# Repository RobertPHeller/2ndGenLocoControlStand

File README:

This is a model diesel locomotive control stand (more or less typical of a 2nd 
generation diesel locomotive).

Files / Directories:

2ndGenLocoControlStand.dxf, 2ndGenLocoControlStand.gcad, and 
2ndGenLocoControlStand.tcl relate to the 3D model of the front panel (based on 
a Hammond Manucafturing RL6685 enclosure).

The ESP32ControlStand directory contains the ESP32 (TTGO-T1) based design, the 
electronics are in KiCad form (Version: 2013.06.11).  The 
ESP32ControlStand/ESP32ControlStand_Node directory contains the OpenMRN code 
(C++, Arduino style using the OpenMRNLite library).

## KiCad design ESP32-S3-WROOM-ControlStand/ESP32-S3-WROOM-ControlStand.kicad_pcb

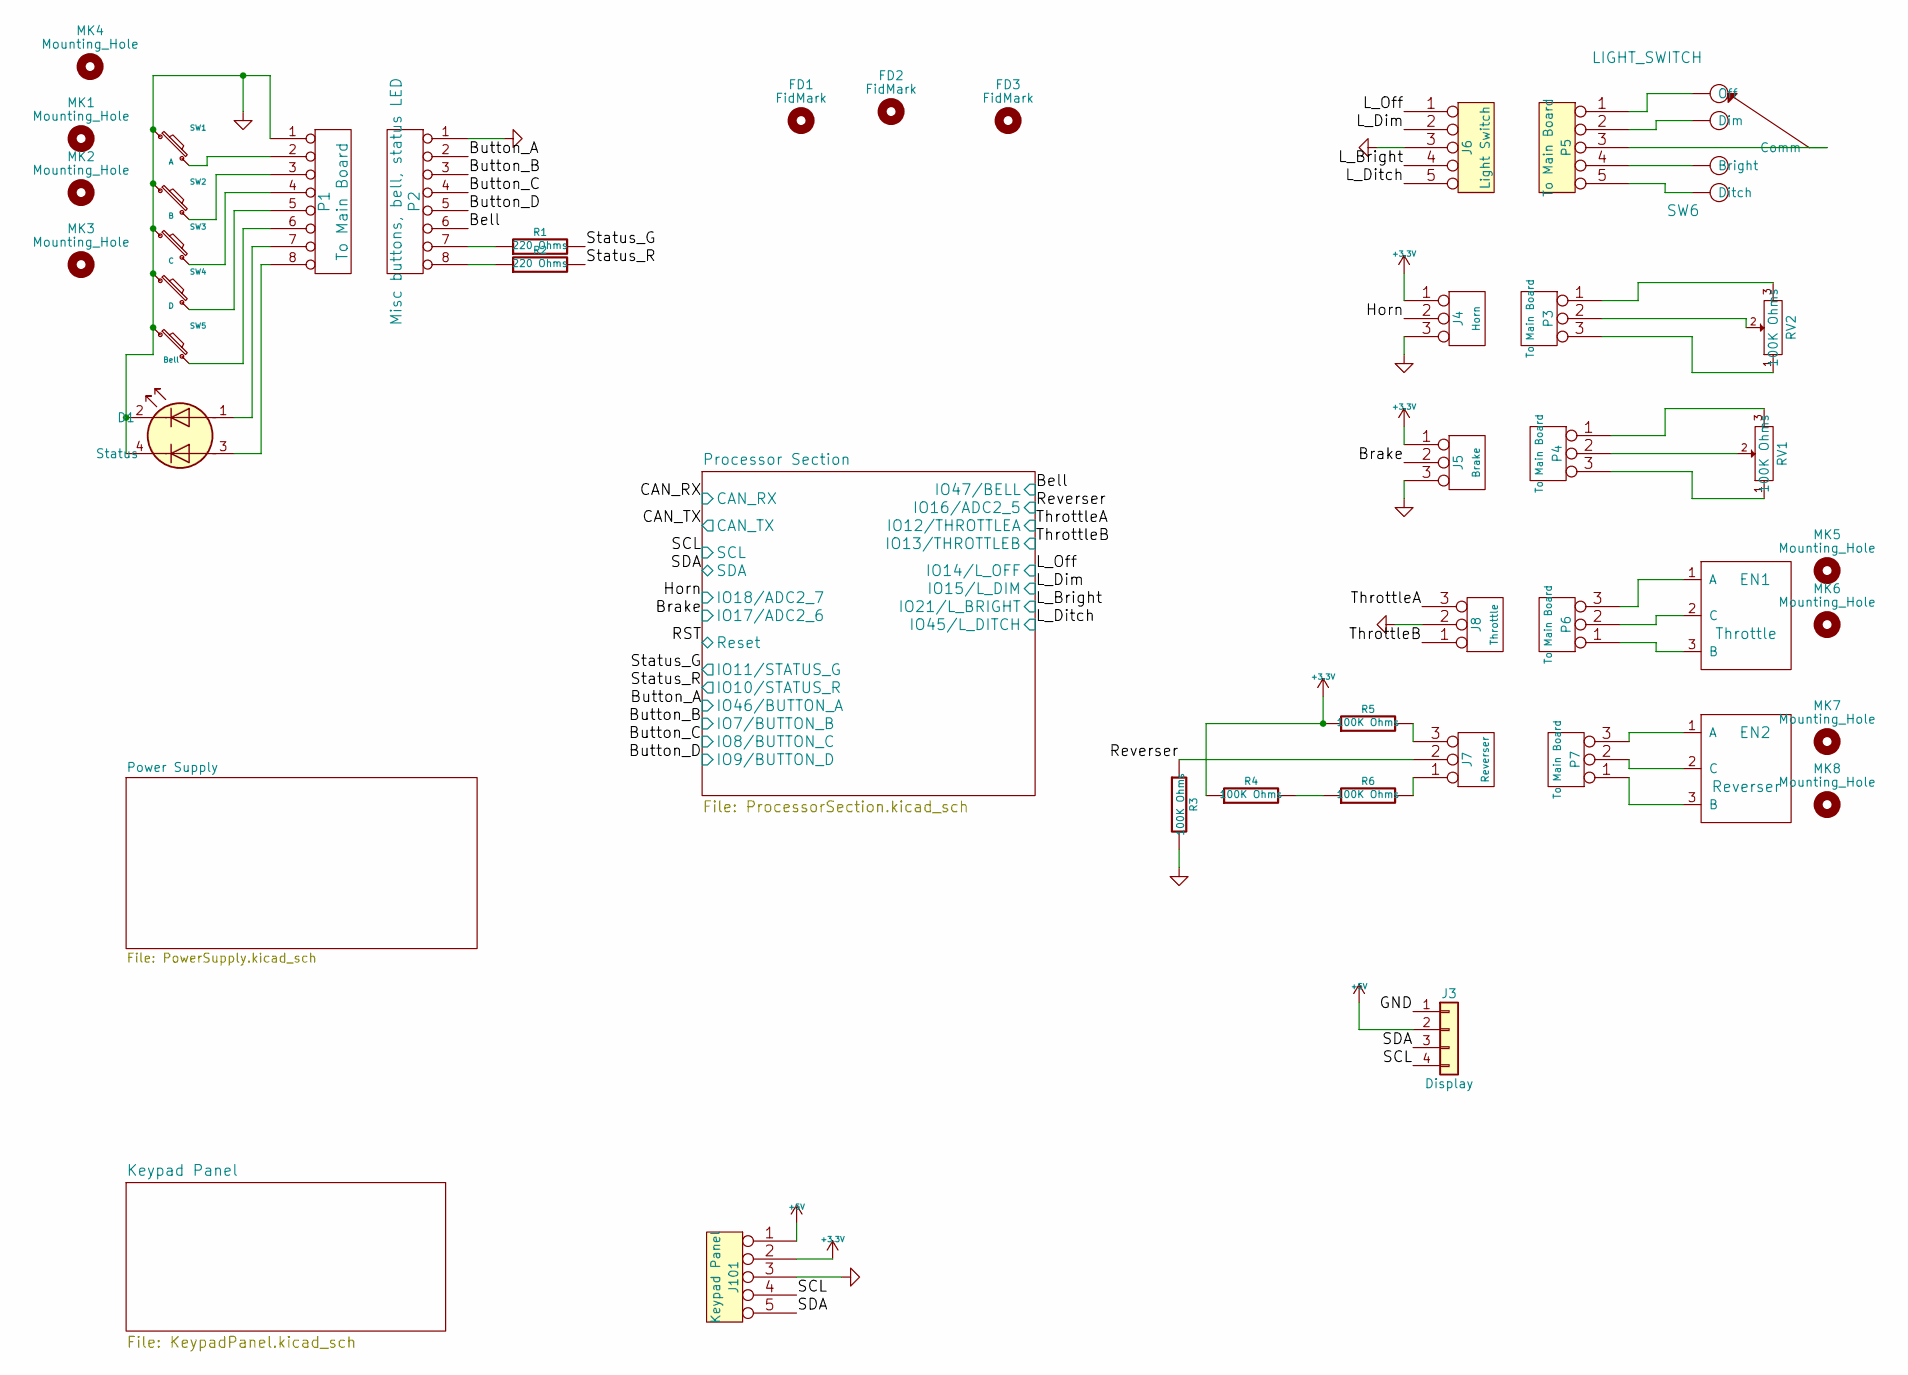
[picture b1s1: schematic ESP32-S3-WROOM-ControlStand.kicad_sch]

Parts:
D1: Status; APHB1608CGKSURKC; Mouser Part Number 604-APHB1608CGKSURKC
EN1: Throttle; Series25L-Encoder; Mouser Part Number 706-25LB10-Q
EN2: Reverser; ALPSEC12C; Mouser Part Number 652-PEC11R4325FN0012
FD1, FD2, FD3: FidMark; Fiducial_1mm_Dia_2.54mm_Outer_CopperTop
J3: Display; JST_PH_B4B-PH-K_1x04_P2.00mm_Vertical; Manufacturer_Part_Number B4B-PH-SM4-TB
J4: Horn; Pin_Header_Straight_1x03_Pitch2.54mm; Mouser Part Number 649-1012937890301BLF
J5: Brake; Pin_Header_Straight_1x03_Pitch2.54mm; Mouser Part Number 649-1012937890301BLF
J6: Light Switch; Pin_Header_Straight_1x05_Pitch2.54mm; Mouser Part Number 523-G800W303018EU
J7: Reverser; Pin_Header_Straight_1x03_Pitch2.54mm; Mouser Part Number 649-1012937890301BLF
J8: Throttle; Pin_Header_Straight_1x03_Pitch2.54mm; Mouser Part Number 649-1012937890301BLF
J101: Keypad Panel; Pin_Header_Straight_1x05_Pitch2.54mm; Mouser Part Number 523-G800W303018EU
MK1, MK2, MK3, MK4, MK5, MK6, MK7, MK8: Mounting_Hole; MountingHole_2.5mm
P1: To Main Board; Pin_Header_Angled_1x08_Pitch2.54mm; Mouser Part Number 649-1012937990801BLF
P2: Misc buttons, bell, status LED; Pin_Header_Straight_1x08_Pitch2.54mm; Mouser Part Number 649-1012937890801BLF
P3, P4, P5: To Main Board
P6, P7: To Main Board; Pin_Header_Angled_1x03_Pitch2.54mm; Mouser Part Number 855-M20-9750346
R1, R2: 220 Ohms; R_0603_1608Metric; Mouser Part Number 603-AC0603FR-07220RL
R3, R4, R5, R6: 100K Ohms; R_0402_1005Metric; Mouser Part Number 279-CRGCQ0402J100K
RV1, RV2: 100K Ohms; Mouser Part Number 774-450T328F104A1A1
SW1: A; SW_SPST_EVQQ2; Mouser Part Number 667-EVQ-Q2U02W
SW2: B; SW_SPST_EVQQ2; Mouser part Number 667-EVQ-Q2U02W
SW3: C; SW_SPST_EVQQ2; Mouser Part Number 667-EVQ-Q2U02W
SW4: D; SW_SPST_EVQQ2; Mouser Part Number 667-EVQ-Q2U02W
SW5: Bell; SW_SPST_EVQQ2; Mouser Part Number 667-EVQ-Q2U02W
SW6: LIGHT_SWITCH

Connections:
+5V: J3.2, J101.1; also elsewhere on the board
/Bell: P2.6; also elsewhere on the board
/Brake: J5.2 (PM); also elsewhere on the board
/Button_A: P2.2; also elsewhere on the board
/Button_B: P2.3; also elsewhere on the board
/Button_C: P2.4; also elsewhere on the board
/Button_D: P2.5; also elsewhere on the board
/Horn: J4.2 (PM); also elsewhere on the board
/L_Bright: J6.4; also elsewhere on the board
/L_Dim: J6.2; also elsewhere on the board
/L_Ditch: J6.5; also elsewhere on the board
/L_Off: J6.1; also elsewhere on the board
/Reverser: J7.2 (PM), R3.1; also elsewhere on the board
/SCL: J3.4, J101.4; also elsewhere on the board
/SDA: J3.3, J101.5; also elsewhere on the board
/Status_G: R1.2; also elsewhere on the board
/Status_R: R2.2; also elsewhere on the board
/ThrottleA: J8.3; also elsewhere on the board
/ThrottleB: J8.1; also elsewhere on the board
GND: D1.2 (K1), D1.4 (K2), J3.1, J4.3, J5.3, J6.3, J8.2 (PM), J101.3, P1.1, P2.1, R3.2, SW1.1, SW2.1, SW3.1, SW4.1, SW5.1; also elsewhere on the board
unnamed: D1.1 (A1), P1.7
unnamed: D1.3 (A2), P1.8
unnamed: EN1.1 (A), P6.3
unnamed: EN1.2 (C), P6.2 (PM)
unnamed: EN1.3 (B), P6.1
unnamed: EN2.1 (A), P7.3
unnamed: EN2.2 (C), P7.2 (PM)
unnamed: EN2.3 (B), P7.1
unnamed: J7.1, R6.2
unnamed: J7.3, R5.2
unnamed: P1.2, SW1.2
unnamed: P1.3, SW2.2
unnamed: P1.4, SW3.2
unnamed: P1.5, SW4.2
unnamed: P1.6, SW5.2
unnamed: P2.7, R1.1
unnamed: P2.8, R2.1
unnamed: P3.1, RV2.3
unnamed: P3.2 (PM), RV2.2
unnamed: P3.3, RV2.1
unnamed: P4.1, RV1.3
unnamed: P4.2 (PM), RV1.2
unnamed: P4.3, RV1.1
unnamed: P5.1, SW6.~
unnamed: P5.2, SW6.~
unnamed: P5.3, SW6.~
unnamed: P5.4, SW6.~
unnamed: P5.5, SW6.~
unnamed: R4.2, R6.1

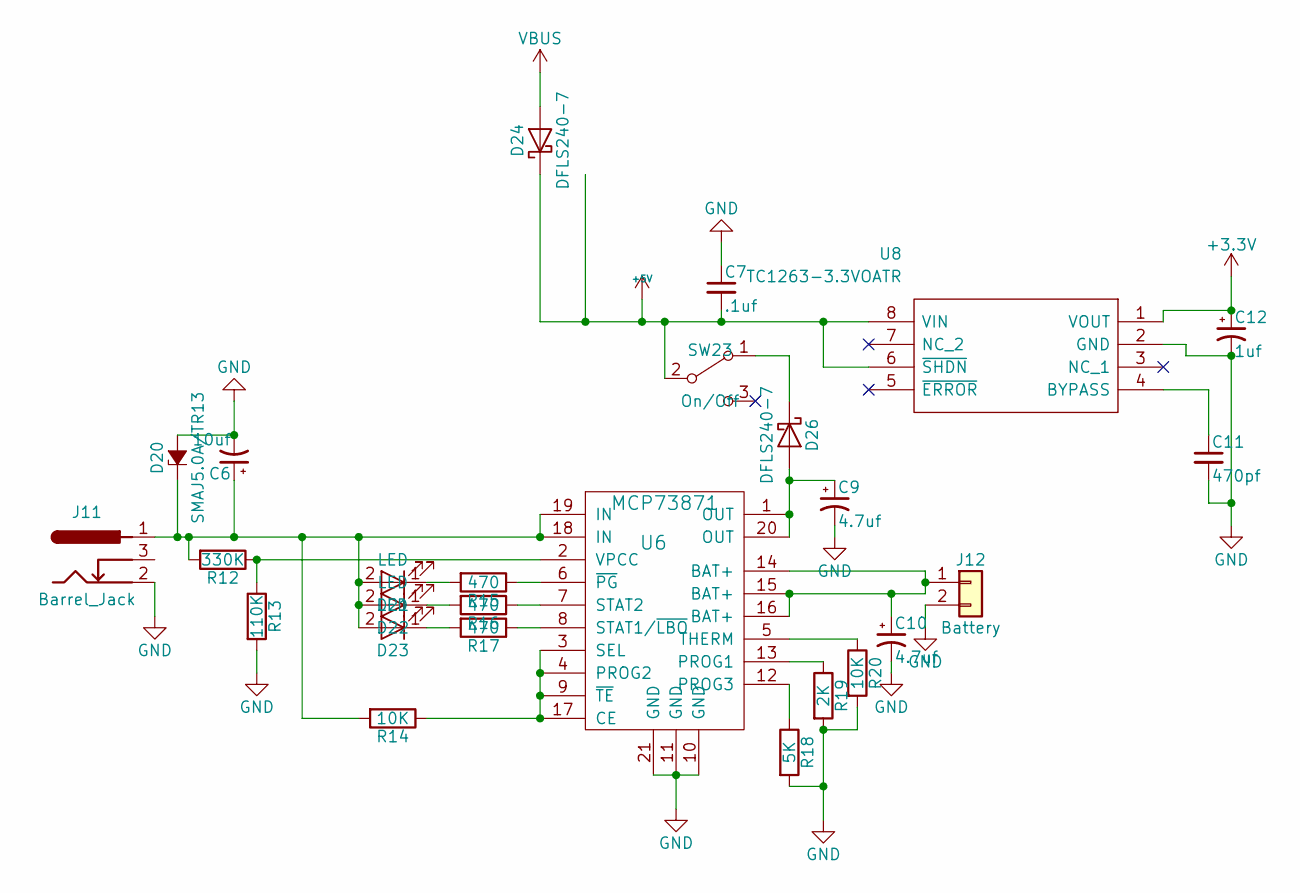
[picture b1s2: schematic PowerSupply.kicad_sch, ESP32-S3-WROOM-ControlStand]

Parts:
C6: 10uf; CP_Elec_4x5.7; Mouser Part Number 710-865080340001
C7: .1uf; C_0402; Mouser Part Number 81-GRM155R62A104KE4J
C9, C10: 4.7uf; CP_Elec_4x5.7; Mouser Part Number 710-865080640004
C11: 470pf; C_0402; Mouser Part Number 80-C0402C471K4RAUTO
C12: 1uf; C_0603_POL; Mouser Part Number 74-TMCJ1C105MTRF
D20: SMAJ5.0A/TR13; D_SMA; Mouser Part Number 603-SMAJ5.0A/TR13
D21: LED; LED_0402; Mouser Part Number 710-150040GS73220
D22: LED; LED_0402; Mouser Part Number 710-150040YS73220
D23: LED; LED_0402; Mouser Part Number 710-150040RS73220
D24, D26: DFLS240-7; D_PowerDI-123; Mouser Part Number 621-DFLS240-7
J11: Barrel_Jack; BARREL_JACK; Mouser Part Number 992-CON-SOCJ-2155
J12: Battery; JST_PH_B2B-PH-K_1x02_P2.00mm_Vertical; Manufacturer_Part_Number B2B-PH-SM4-TB
R12: 330K; R_0402; Mouser Part Number 603-AF0402FR-07330KL
R13: 110K; R_0402; Mouser Part Number 603-RC0402JR-13110KL
R14, R20: 10K; R_0402; Mouser Part Number 603-RC0402JR-0710KL
R15, R16, R17: 470; R_0402; Mouser Part Number 603-RC0402JR-07470RL
R18: 5K; R_0402; Mouser Part Number 603-RC0402FR-075KL
R19: 2K; R_0402; Mouser Part Number 603-RC0402FR-132KL
SW23: On/Off; SW_SPDT_CK-JS102011SAQN; Mouser Part Number 611-JS102011SAQN
U6: MCP73871; QFN-20-1EP_4x4mm_P0.5mm_EP2.5x2.5mm_ThermalVias; Mouser Part Number 579-MCP73871-3CAI/ML
U8: TC1263-3.3VOATR; SOIC-8W_5.3x5.3mm_P1.27mm; Manufacturer_Part_Number TC1263-3.3VOATR

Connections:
+5V: C7.2, D24.1 (K), SW23.2 (B), U8.6 (~SHDN), U8.8 (VIN); also elsewhere on the board
GND: C6.2, C7.1, C9.2, C10.2, C11.2, C12.2, D20.2 (A), J11.2, J12.2, R13.2, R18.2, R19.2, R20.2, U6.10 (GND), U6.11 (GND), U6.21 (GND), U8.2 (GND); also elsewhere on the board
unnamed: C6.1, D20.1 (K), D21.2 (A), D22.2 (A), D23.2 (A), J11.1, R12.2, R14.2, U6.18 (IN), U6.19 (IN)
unnamed: C9.1, D26.2 (A), U6.1 (OUT), U6.20 (OUT)
unnamed: C10.1, J12.1, U6.14 (BAT+), U6.15 (BAT+), U6.16 (BAT+)
unnamed: C11.1, U8.4 (BYPASS)
unnamed: D21.1 (K), R15.2
unnamed: D22.1 (K), R16.2
unnamed: D23.1 (K), R17.2
unnamed: D26.1 (K), SW23.1 (A)
unnamed: R12.1, R13.1, U6.2 (VPCC)
unnamed: R14.1, U6.3 (SEL), U6.4 (PROG2), U6.9 (~TE), U6.17 (CE)
unnamed: R15.1, U6.6 (~PG)
unnamed: R16.1, U6.7 (STAT2)
unnamed: R17.1, U6.8 (STAT1/~LBO)
unnamed: R18.1, U6.12 (PROG3)
unnamed: R19.1, U6.13 (PROG1)
unnamed: R20.1, U6.5 (THERM)
VBUS: D24.2 (A); also elsewhere on the board

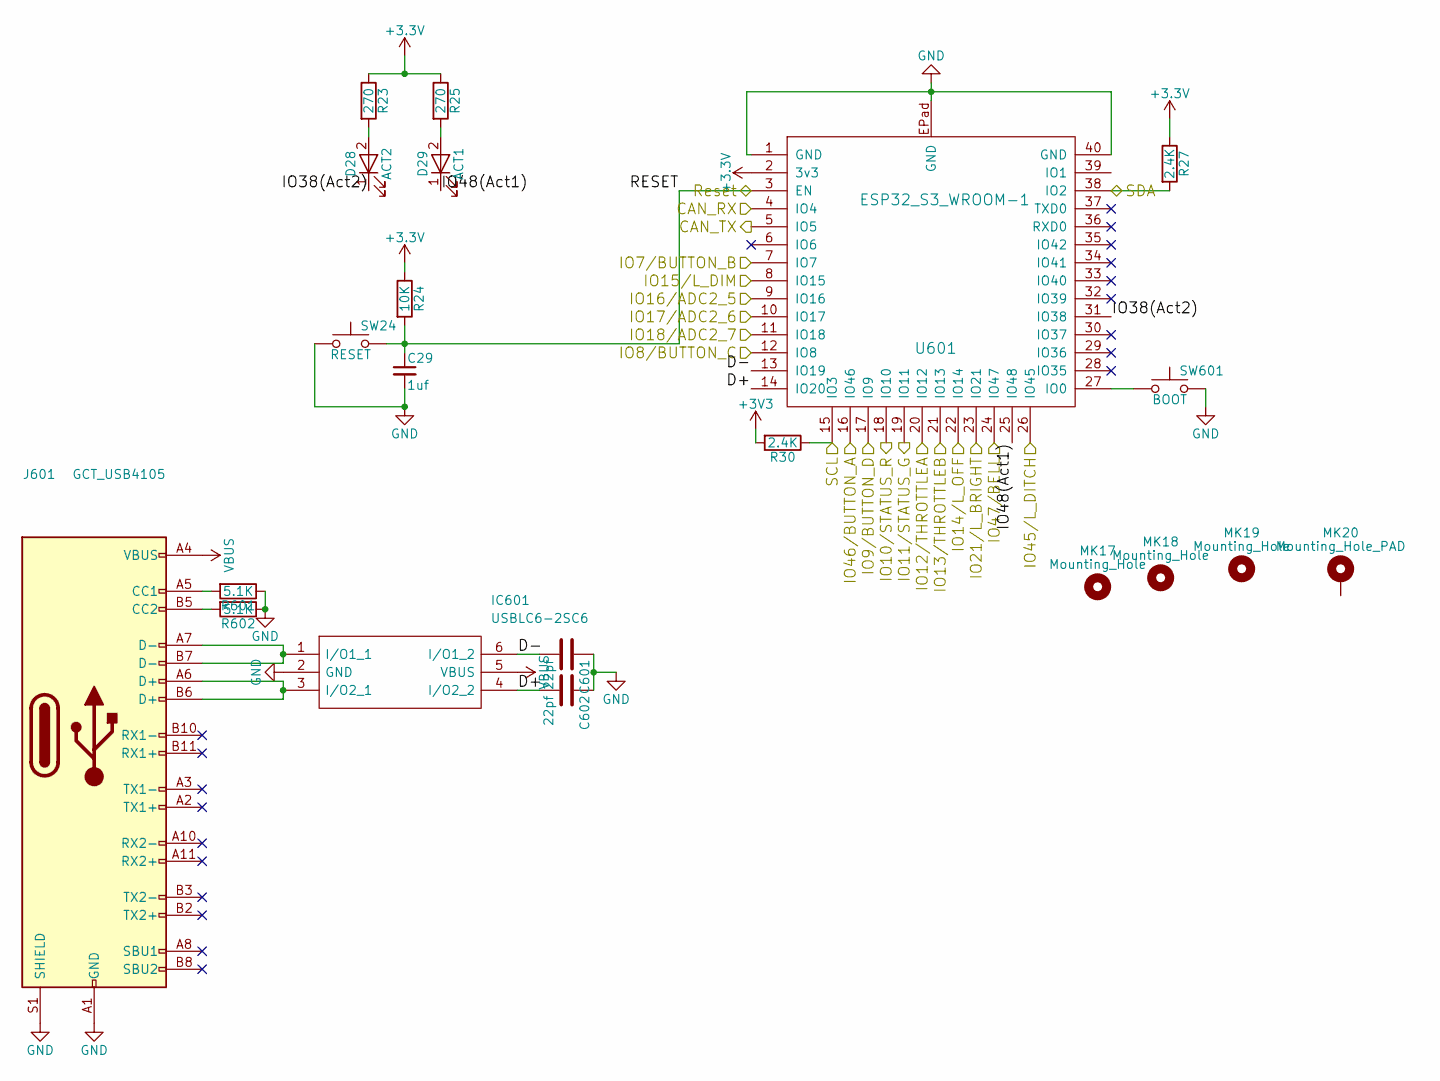
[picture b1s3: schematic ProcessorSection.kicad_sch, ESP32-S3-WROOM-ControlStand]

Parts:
C29: 1uf; C_0402; Mouser Part Number 80-C0402C101K8RAUTO
C601, C602: 22pf; C_0402; Mouser Part Number 187-CL05C220JB5NNND
D28: ACT2; LED_0402; Mouser Part Number 710-150040SS73220
D29: ACT1; LED_0402; Mouser Part Number 710-150040GS73220
IC601: USBLC6-2SC6; SOT-23-6; Mouser2 Part Number 511-USBLC6-2SC6
J601: GCT_USB4105; USB_C_Receptacle_GCT_USB4105-xx-A_16P_TopMnt_Horizontal
MK17, MK18, MK19: Mounting_Hole; MountingHole_2.5mm
MK20: Mounting_Hole_PAD; MountingHole_2.5mm_Pad
R23, R25: 270; R_0402; Mouser Part Number 754-RR0510P-271D
R24: 10K; R_0402; Mouser Part Number 603-RC0402JR-1310KL
R27, R30: 2.4K; R_0402; Mouser Part Number 71-CRCW06032K40JNEAC
R601, R602: 5.1K; R_0402; Mouser Part Number 71-CRCW0402-5.1K-E3
SW24: RESET; SW_SPST_PTS810; Mouser Part Number 611-PTS810SJM250SMTR
SW601: BOOT; SW_SPST_PTS810; Mouser Part Number 611-PTS810SJM250SMTR
U601: ESP32_S3_WROOM-1; Mouser Part Number 356-ESP32-S3WROOM1N4

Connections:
/Bell: U601.24 (IO47); also elsewhere on the board
/Brake: U601.10 (IO17); also elsewhere on the board
/Button_A: U601.16 (IO46); also elsewhere on the board
/Button_B: U601.7 (IO7); also elsewhere on the board
/Button_C: U601.12 (IO8); also elsewhere on the board
/Button_D: U601.17 (IO9); also elsewhere on the board
/CAN_RX: U601.4 (IO4)
/CAN_TX: U601.5 (IO5)
/Horn: U601.11 (IO18); also elsewhere on the board
/L_Bright: U601.23 (IO21); also elsewhere on the board
/L_Dim: U601.8 (IO15); also elsewhere on the board
/L_Ditch: U601.26 (IO45); also elsewhere on the board
/L_Off: U601.22 (IO14); also elsewhere on the board
/Processor Section/D+: C602.2, IC601.4 (I/O2_2), U601.14 (IO20)
/Processor Section/D-: C601.2, IC601.6 (I/O1_2), U601.13 (IO19)
/Processor Section/IO38(Act2): D28.1 (K), U601.31 (IO38)
/Processor Section/IO48(Act1): D29.1 (K), U601.25 (IO48)
/RST: C29.1, R24.2, SW24.2, U601.3 (EN)
/Reverser: U601.9 (IO16); also elsewhere on the board
/SCL: R30.1, U601.15 (IO3); also elsewhere on the board
/SDA: R27.2, U601.38 (IO2); also elsewhere on the board
/Status_G: U601.19 (IO11); also elsewhere on the board
/Status_R: U601.18 (IO10); also elsewhere on the board
/ThrottleA: U601.20 (IO12); also elsewhere on the board
/ThrottleB: U601.21 (IO13); also elsewhere on the board
GND: C29.2, C601.1, C602.1, IC601.2 (GND), J601.A1 (GND), J601.A12 (GND), J601.B1 (GND), J601.B12 (GND), J601.S1 (SHIELD), R601.1, R602.1, SW24.1, SW601.2, U601.1 (GND), U601.40 (GND), U601.EPad (GND); also elsewhere on the board
unnamed: D28.2 (A), R23.2
unnamed: D29.2 (A), R25.2
unnamed: IC601.1 (I/O1_1), J601.A7 (D-), J601.B7 (D-)
unnamed: IC601.3 (I/O2_1), J601.A6 (D+), J601.B6 (D+)
unnamed: J601.A5 (CC1), R601.2
unnamed: J601.B5 (CC2), R602.2
unnamed: SW601.1, U601.27 (IO0)
VBUS: IC601.5 (VBUS), J601.A4 (VBUS), J601.A9 (VBUS), J601.B4 (VBUS), J601.B9 (VBUS); also elsewhere on the board

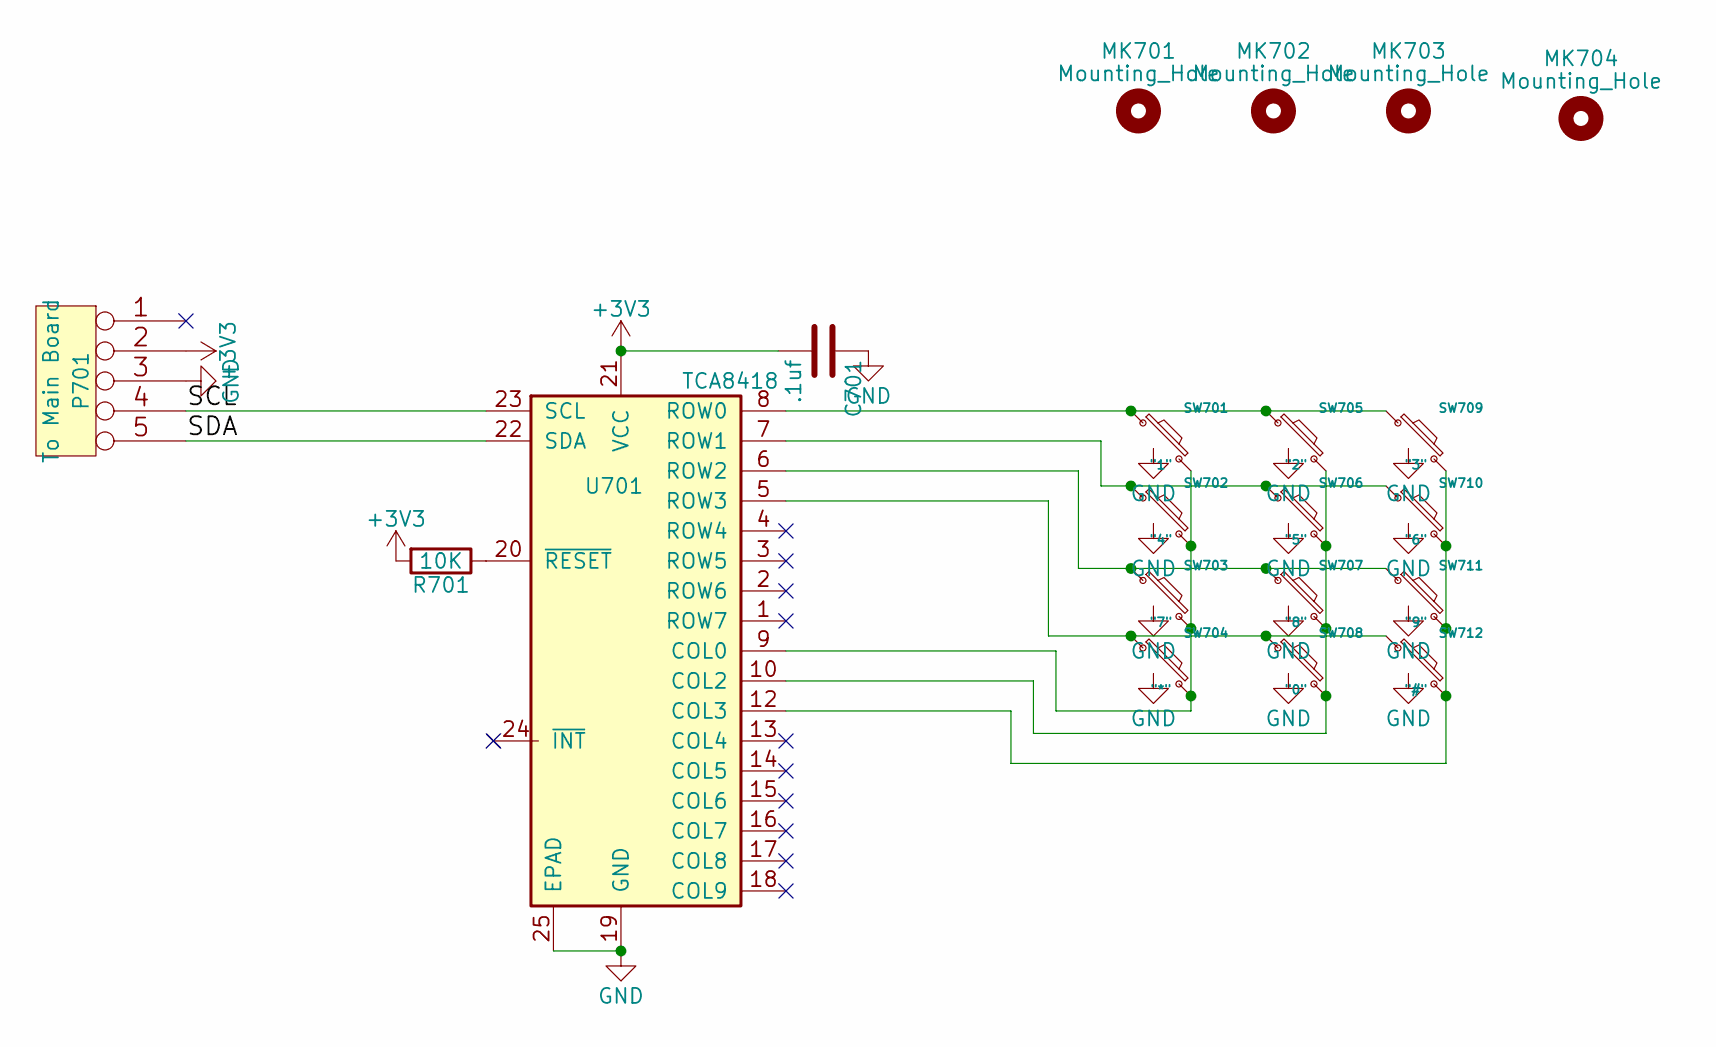
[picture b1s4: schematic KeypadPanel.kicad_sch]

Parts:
C701: .1uf; C_0603_1608Metric; Mouser Part Number 810-C0603X5R1E104KBB
MK701, MK702, MK703, MK704: Mounting_Hole; MountingHole_2.5mm
P701: To Main Board; Pin_Header_Angled_1x05_Pitch2.54mm; Mouser Part Number 649-1012937990501BLF
R701: 10K; R_0603_1608Metric; Mouser Part Number 71-CRCW0603J-910K-E3
SW701: "1"; SW_SPST_B3U-1100P-B; Mouser Part Number 653-B3U-1100P-B
SW702: "4"; SW_SPST_B3U-1100P-B; Mouser Part Number 653-B3U-1100P-B
SW703: "7"; SW_SPST_B3U-1100P-B; Mouser Part Number 653-B3U-1100P-B
SW704: "*"; SW_SPST_B3U-1100P-B; Mouser Part Number 653-B3U-1100P-B
SW705: "2"; SW_SPST_B3U-1100P-B; Mouser Part Number 653-B3U-1100P-B
SW706: "5"; SW_SPST_B3U-1100P-B; Mouser Part Number 653-B3U-1100P-B
SW707: "8"; SW_SPST_B3U-1100P-B; Mouser Part Number 653-B3U-1100P-B
SW708: "0"; SW_SPST_B3U-1100P-B; Mouser Part Number 653-B3U-1100P-B
SW709: "3"; SW_SPST_B3U-1100P-B; Mouser Part Number 653-B3U-1100P-B
SW710: "6"; SW_SPST_B3U-1100P-B; Mouser Part Number 653-B3U-1100P-B
SW711: "9"; SW_SPST_B3U-1100P-B; Mouser Part Number 653-B3U-1100P-B
SW712: "#"; SW_SPST_B3U-1100P-B; Mouser Part Number 653-B3U-1100P-B
U701: TCA8418; QFN-24-1EP_4x4mm_P0.5mm_EP2.7x2.7mm_ThermalVias

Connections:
/Keypad Panel/SCL: P701.4, U701.23 (SCL)
/Keypad Panel/SDA: P701.5, U701.22 (SDA)
GND: C701.1, P701.3, SW701.3 (GND), SW702.3 (GND), SW703.3 (GND), SW704.3 (GND), SW705.3 (GND), SW706.3 (GND), SW707.3 (GND), SW708.3 (GND), SW709.3 (GND), SW710.3 (GND), SW711.3 (GND), SW712.3 (GND), U701.19 (GND), U701.25 (EPAD); also elsewhere on the board
unnamed: R701.1, U701.20 (~RESET)
unnamed: SW701.1, SW705.1, SW709.1, U701.8 (ROW0)
unnamed: SW701.2, SW702.2, SW703.2, SW704.2, U701.9 (COL0)
unnamed: SW702.1, SW706.1, SW710.1, U701.7 (ROW1)
unnamed: SW703.1, SW707.1, SW711.1, U701.6 (ROW2)
unnamed: SW704.1, SW708.1, SW712.1, U701.5 (ROW3)
unnamed: SW705.2, SW706.2, SW707.2, SW708.2, U701.10 (COL2)
unnamed: SW709.2, SW710.2, SW711.2, SW712.2, U701.12 (COL3)

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
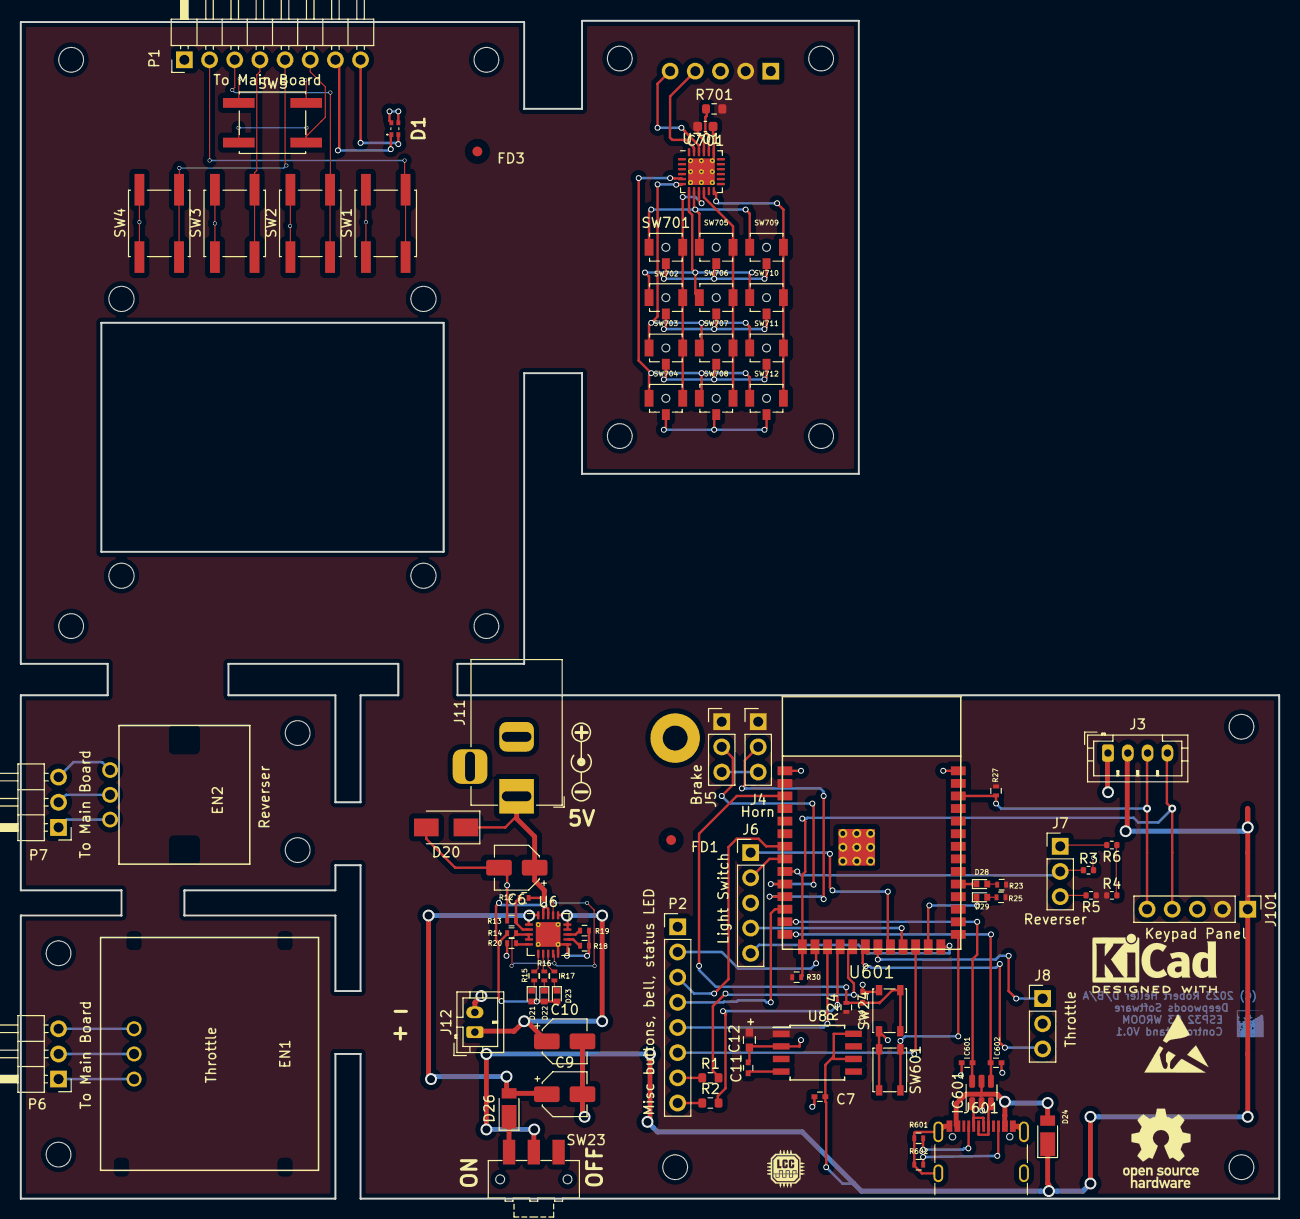
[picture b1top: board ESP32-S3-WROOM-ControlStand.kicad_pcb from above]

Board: 2 copper layers, 127.0 x 118.9 mm, 102 parts (1 on the bottom side), 78 nets.

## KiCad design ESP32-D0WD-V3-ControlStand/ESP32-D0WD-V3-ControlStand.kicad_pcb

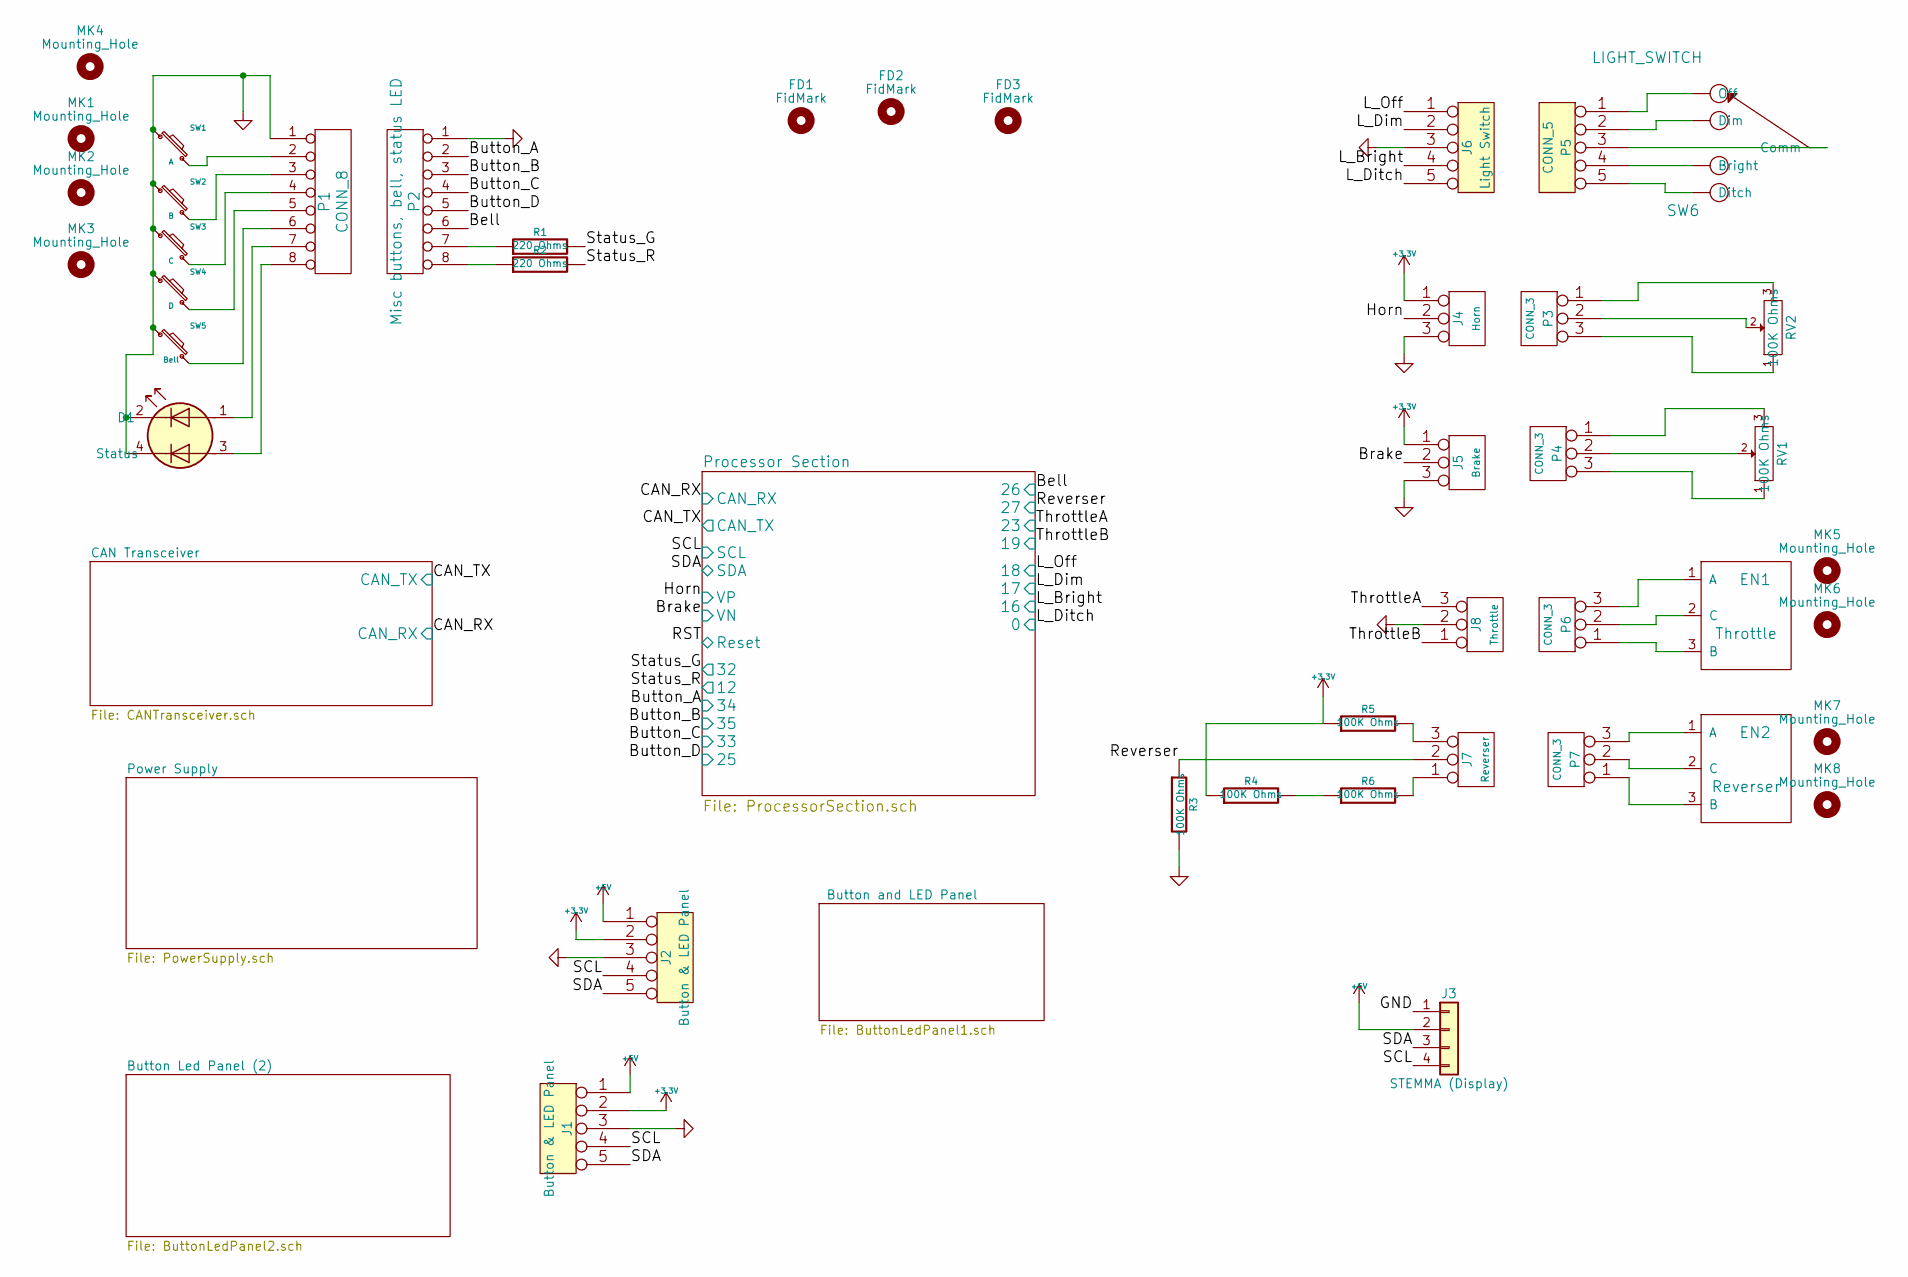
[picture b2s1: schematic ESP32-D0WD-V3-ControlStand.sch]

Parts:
D1: Status; APHB1608CGKSURKC; Mouser Part Number 604-APHB1608CGKSURKC
EN1: Throttle; Series25L-Encoder; Mouser Part Number 706-25LB10-Q
EN2: Reverser; ALPSEC12C; Mouser Part Number 652-PEC11R4325FN0012
FD1, FD2, FD3: FidMark; Fiducial_1mm_Dia_2.54mm_Outer_CopperTop
J1, J2: Button & LED Panel; Pin_Header_Straight_1x05_Pitch2.54mm; Mouser Part Number 523-G800W303018EU
J3: STEMMA (Display); JST_PH_B4B-PH-SM4-TB_04x2.00mm_Straight; Manufacturer_Part_Number B4B-PH-SM4-TB
J4: Horn; Pin_Header_Straight_1x03_Pitch2.54mm; Mouser Part Number 649-1012937890301BLF
J5: Brake; Pin_Header_Straight_1x03_Pitch2.54mm; Mouser Part Number 649-1012937890301BLF
J6: Light Switch; Pin_Header_Straight_1x05_Pitch2.54mm; Mouser Part Number 523-G800W303018EU
J7: Reverser; Pin_Header_Straight_1x03_Pitch2.54mm; Mouser Part Number 649-1012937890301BLF
J8: Throttle; Pin_Header_Straight_1x03_Pitch2.54mm; Mouser Part Number 649-1012937890301BLF
MK1, MK2, MK3, MK4, MK5, MK6, MK7, MK8: Mounting_Hole; MountingHole_2.5mm
P1: CONN_8; Pin_Header_Angled_1x08_Pitch2.54mm; Mouser Part Number 649-1012937990801BLF
P2: Misc buttons, bell, status LED; Pin_Header_Straight_1x08_Pitch2.54mm; Mouser Part Number 649-1012937890801BLF
P3, P4: CONN_3
P5: CONN_5
P6, P7: CONN_3; Pin_Header_Angled_1x03_Pitch2.54mm; Mouser Part Number 855-M20-9750346
R1, R2: 220 Ohms; R_0603; Mouser Part Number 603-AC0603FR-07220RL
R3, R4, R5, R6: 100K Ohms; R_0402; Mouser Part Number 279-CRGCQ0402J100K
RV1, RV2: 100K Ohms; Mouser Part Number 774-450T328F104A1A1
SW1: A; SW_SPST_EVQQ2; Mouser Part Number 667-EVQ-Q2U02W
SW2: B; SW_SPST_EVQQ2; Mouser part Number 667-EVQ-Q2U02W
SW3: C; SW_SPST_EVQQ2; Mouser Part Number 667-EVQ-Q2U02W
SW4: D; SW_SPST_EVQQ2; Mouser Part Number 667-EVQ-Q2U02W
SW5: Bell; SW_SPST_EVQQ2; Mouser Part Number 667-EVQ-Q2U02W
SW6: LIGHT_SWITCH

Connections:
+3V3: J1.2, J2.2, J4.1, J5.1, R4.1, R5.1; also elsewhere on the board
+5V: J1.1, J2.1, J3.2; also elsewhere on the board
/Bell: P2.6; also elsewhere on the board
/Brake: J5.2 (PM); also elsewhere on the board
/Button_A: P2.2; also elsewhere on the board
/Button_B: P2.3; also elsewhere on the board
/Button_C: P2.4; also elsewhere on the board
/Button_D: P2.5; also elsewhere on the board
/Horn: J4.2 (PM); also elsewhere on the board
/L_Bright: J6.4; also elsewhere on the board
/L_Dim: J6.2; also elsewhere on the board
/L_Ditch: J6.5; also elsewhere on the board
/L_Off: J6.1; also elsewhere on the board
/Reverser: J7.2 (PM), R3.1; also elsewhere on the board
/SCL: J1.4, J2.4, J3.4; also elsewhere on the board
/SDA: J1.5, J2.5, J3.3; also elsewhere on the board
/Status_G: R1.2; also elsewhere on the board
/Status_R: R2.2; also elsewhere on the board
/ThrottleA: J8.3; also elsewhere on the board
/ThrottleB: J8.1; also elsewhere on the board
GND: D1.2 (K1), D1.4 (K2), J1.3, J2.3, J3.1, J4.3, J5.3, J6.3, J8.2 (PM), P1.1, P2.1, R3.2, SW1.1, SW2.1, SW3.1, SW4.1, SW5.1; also elsewhere on the board
unnamed: D1.1 (A1), P1.7
unnamed: D1.3 (A2), P1.8
unnamed: EN1.1 (A), P6.3
unnamed: EN1.2 (C), P6.2 (PM)
unnamed: EN1.3 (B), P6.1
unnamed: EN2.1 (A), P7.3
unnamed: EN2.2 (C), P7.2 (PM)
unnamed: EN2.3 (B), P7.1
unnamed: J7.1, R6.2
unnamed: J7.3, R5.2
unnamed: P1.2, SW1.2
unnamed: P1.3, SW2.2
unnamed: P1.4, SW3.2
unnamed: P1.5, SW4.2
unnamed: P1.6, SW5.2
unnamed: P2.7, R1.1
unnamed: P2.8, R2.1
unnamed: P3.1, RV2.3
unnamed: P3.2 (PM), RV2.2
unnamed: P3.3, RV2.1
unnamed: P4.1, RV1.3
unnamed: P4.2 (PM), RV1.2
unnamed: P4.3, RV1.1
unnamed: P5.1, SW6.~
unnamed: P5.2, SW6.~
unnamed: P5.3, SW6.~
unnamed: P5.4, SW6.~
unnamed: P5.5, SW6.~
unnamed: R4.2, R6.1

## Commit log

2019-10-01 Initial Commit.
2019-10-01 Start ESP32ControlStand.
2019-10-02 ESP32ControlStand Base I/O circuits.
2019-10-03 Completed first draft of PCBs for ESP32ControlStand.
2019-10-03 Tweaks of PCBs for ESP32ControlStand.
2019-10-04 First draft of lid cutout model
2019-10-04 Assorted updates to the PCB.
2019-10-05 Continue 3D model, spec out horn and brake pots, noturn hole for reverser.
2019-10-05 Continue 3D model.
2019-10-06 Continue 3D model (nearly finished).
2019-10-06 3D Model nearly complete, DXF export.
2019-10-06 Initial sketches (firmware).
2019-10-06 Complete first draft of test program.
2019-10-07 Fleshing out the ESP32ControlStand Node code.
2019-10-07 Add NODEID.h
2019-10-07 Generate PDF of schematic, PNG of board.
2019-10-07 Add README
2019-10-07 Continue to fleshout the the throttle node.
2019-10-07 Start on ESP32ControlStand class (derived from TractionThrottle).
2019-10-07 Working on ESP32ControlStand class (derived from TractionThrottle).
2019-10-08 First complete compile of Throttle Node code.
2019-10-09 Ready to start writing menu / display code.
2019-10-09 Continuing to flesh out the firmware.
2019-10-11 Continuing to flesh out the firmware. Loco Browse Screen done.
2019-10-11 Start a fritzing breadboard.
2019-10-12 Update circuit to use "Default" SDA/SDL.
2019-10-12 Continue to flesh out the firmware: add config options, remove unneeded release train function, remove redundant currentTrain_ variable.
2019-10-12 Tweaks to the SNIP flow.
2019-10-12 Fix I/O conflict (Status_G).
2019-10-12 Complete phase1 (buttons and display) breadboard.
2019-10-13 Continuing with the breadboard.
2019-10-14 Tweaks to the poll_33h function and train speed update.
2019-10-14 Search Screen done.
2019-10-16 Set things up to use the status LED.
2019-10-16 Finish up throttle code.
2019-10-16 Complete fritzing breadboard.
2019-10-21 Add Emergency Stop button.
2019-10-22 Completed Function Screen.
2020-12-23 FreeCAD model of the box lid.
2020-12-26 Continue FreeCAD work
2020-12-28 Horn lever in place.
2022-02-06 Add I2C pullups.
2022-07-25 Start on bare processor, smd version.
2022-07-26 Nearly complete schematic. Added Antenna footprint.
2022-07-27 Conversion to SMD continues...
2022-07-28 Complete PS, work on parts spec.
2022-07-28 Transfer edge cuts.
2022-07-29 Completed parts spec for ESP32-D0WD-V3-ControlStand.
2022-07-31 Working on the PCB Layout.
2022-07-31 Completed V0.0 PCB.
2022-07-31 Started on V0.1 PCB.
2022-08-01 About halfway done.
2022-08-01 Nearly done. Just the button/LED boards to do.
2022-08-02 Completed V0-1 board (still need to add a few things -- logos and such and adjust silk).
2022-08-02 Completed V0-1 board -- added logos, cleaned up silk, added connector labels, etc.
2022-08-02 Add measurments (for CAD work on a hand-held box/enclusure).
2022-08-03 Working on CAD: handheld box.
2022-08-06 Working on CAD models.
2022-08-07 Working on CAD for hand held boxes.
2022-08-09 Working on control features CAD.
2022-12-09 Created ESP32-S3-WROOM-ControlStand.
2022-12-10 Add Keypad board.
2022-12-12 Start on OpenMRNIDF port of Control Stand (Throttle) firmware.
2022-12-16 Rename code directory.
2022-12-16 More code rearangement and updates.
2022-12-17 Update CDI (XML) Data handling.
2022-12-18 Complete NvsManager.
2022-12-19 Update to CAD: Keypad board support.
2022-12-21 Add additional dims.
2022-12-21 Add extruded labels on the keypad buttons.
2022-12-21 Complete STL generation.
2022-12-21 Updates to sdkconfig.defaults: serial JTAG
2022-12-22 Add brake lever, update STL code for levers.
2022-12-26 Completed basic Control Stand (throttle) code. TODO: Keypad processing.
2022-12-26 Starting to add the horn control.
2022-12-27 Add horn button.
2022-12-27 Added keypad functionallity.
2023-02-09 Add ESP32-T7S3-ControlStand.
2023-02-09 Update .gitignore.
2023-04-29 Transition to esp idf V5.0.1.
2023-04-30 Update: remove USB connector from main board and update for current Adafruit OLED.
2023-05-01 Add Light Switch.
2023-05-02 Add Light Switch Knob.
2024-02-18 Adjust post positions.
2024-02-19 update ESP32-T7S3-ControlStand: Kicad 6, fix SDA, clean up and finalize PCB.
2024-04-08 Snapshot April 8, 2024.
2024-04-08 3D models mostly done.
2024-04-09 Add USB connector w/cutout. Add battery w/cover.
2024-04-25 Finalize part numbers for BOM.

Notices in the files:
ESP32-D0WD-V3-ControlStand/ESP32-D0WD-V3-ControlStand.kicad_pcb:
(C) 2022 Robert Heller D/B/A
ESP32-S3-WROOM-ControlStand/ESP32-S3-WROOM-ControlStand.kicad_pcb:
(C) 2023 Robert Heller D/B/A
